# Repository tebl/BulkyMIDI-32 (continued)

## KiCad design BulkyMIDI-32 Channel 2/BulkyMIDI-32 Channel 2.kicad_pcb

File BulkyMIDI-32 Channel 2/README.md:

# BulkyMIDI-32 Channel 2
I know that the main *BulkyMIDI-32* has a fancy display that shows instruments and so on, the original *Roland MT-32* also did something similar back when they were still sold in music shops. However, I wanted an excuse to add a ton of LEDs to the project while having a bit of fun with older logic chips. Because, who doesn't want more blinking lights? Noone, that's who. The other channel monitor board is a bit more interesting in that it does everything with basic logic chips, but I wanted one more variant to play around - this one uses an Arduino instead.

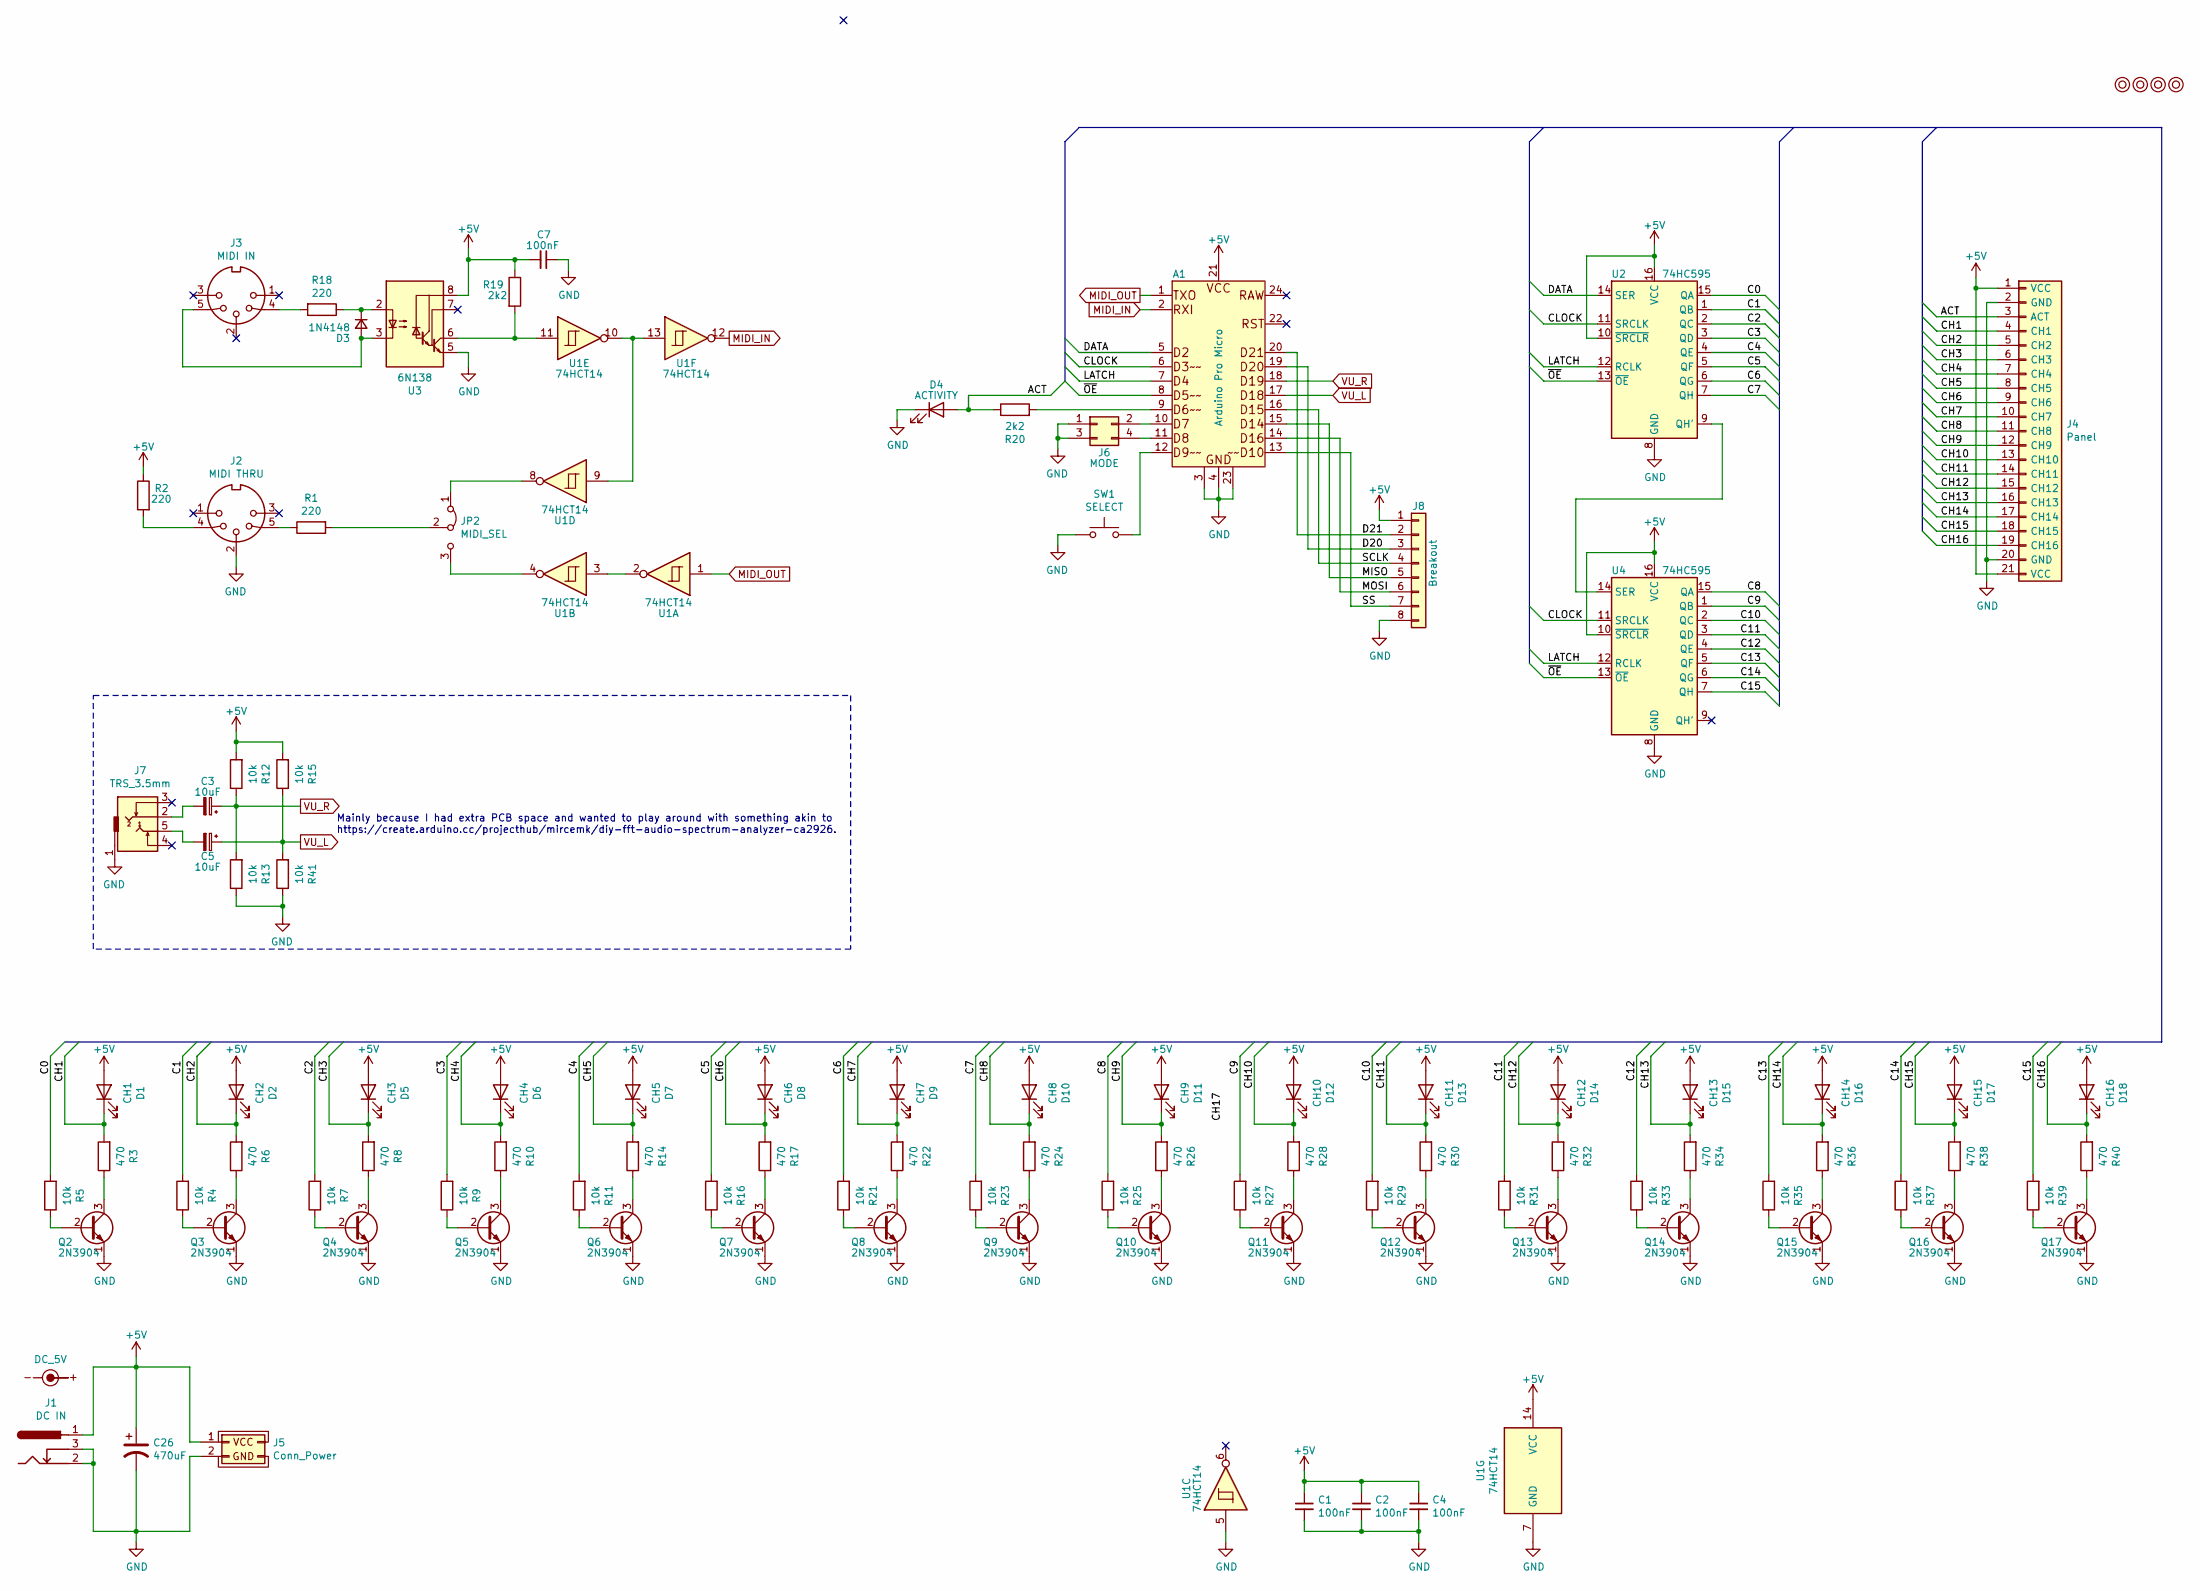
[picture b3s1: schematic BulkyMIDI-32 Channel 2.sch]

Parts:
A1: Arduino Pro Micro; Arduino_Pro_Micro
C1, C2, C4, C7: 100nF; C_Disc_D4.7mm_W2.5mm_P5.00mm
C3, C5: 10uF; CP_Radial_D4.0mm_P2.00mm
C26: 470uF; CP_Radial_D8.0mm_P3.50mm
D1: CH1; LED_D3.0mm
D2: CH2; LED_D3.0mm
D3: 1N4148; D_DO-35_SOD27_P7.62mm_Horizontal
D4: ACTIVITY; LED_D3.0mm
D5: CH3; LED_D3.0mm
D6: CH4; LED_D3.0mm
D7: CH5; LED_D3.0mm
D8: CH6; LED_D3.0mm
D9: CH7; LED_D3.0mm
D10: CH8; LED_D3.0mm
D11: CH9; LED_D3.0mm
D12: CH10; LED_D3.0mm
D13: CH11; LED_D3.0mm
D14: CH12; LED_D3.0mm
D15: CH13; LED_D3.0mm
D16: CH14; LED_D3.0mm
D17: CH15; LED_D3.0mm
D18: CH16; LED_D3.0mm
J1: DC IN; BarrelJack_Horizontal
J2: MIDI THRU; DIN5_MIDI
J3: MIDI IN; DIN5_MIDI
J4: Panel; Channel_Panel
J5: Conn_Power
J6: MODE; PinHeader_2x02_P2.54mm_Horizontal
J7: TRS_3.5mm; Tayda_3.5mm_stereo_TRS_jack_A-853
J8: Breakout; PinHeader_1x08_P2.54mm_Vertical
JP2: MIDI_SEL; PinHeader_1x03_P2.54mm_Horizontal
M1, M2, M3, M4: Mounting; M3
Q2, Q3, Q4, Q5, Q6, Q7, Q8, Q9, Q10, Q11, Q12, Q13, Q14, Q15, Q16, Q17: 2N3904; TO-92_Inline_Wide
R1, R2, R18: 220; R_Axial_DIN0207_L6.3mm_D2.5mm_P10.16mm_Horizontal
R3, R6, R8, R10, R14, R17, R22, R24, R26, R28, R30, R32, R34, R36, R38, R40: 470; R_Axial_DIN0207_L6.3mm_D2.5mm_P10.16mm_Horizontal
R4, R5, R7, R9, R11, R12, R13, R15, R16, R21, R23, R25, R27, R29, R31, R33, R35, R37, R39, R41: 10k; R_Axial_DIN0207_L6.3mm_D2.5mm_P10.16mm_Horizontal
R19, R20: 2k2; R_Axial_DIN0207_L6.3mm_D2.5mm_P10.16mm_Horizontal
SW1: SELECT; SW_Tactile_SPST_Angled_PTS645Vx39-2LFS
SYM1: DC_5V; PWR_Specification
U1: 74HCT14; DIP-14_W7.62mm_Socket_LongPads
U2, U4: 74HC595; DIP-16_W7.62mm_Socket_LongPads
U3: 6N138; DIP-8_W7.62mm_Socket_LongPads

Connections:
+5V: A1.21 (VCC), C1.1, C2.1, C4.1, C7.2, C26.1, D1.2 (A), D2.2 (A), D5.2 (A), D6.2 (A), D7.2 (A), D8.2 (A), D9.2 (A), D10.2 (A), D11.2 (A), D12.2 (A), D13.2 (A), D14.2 (A), D15.2 (A), D16.2 (A), D17.2 (A), D18.2 (A), J1.1, J4.1 (VCC), J4.21 (VCC), J5.1 (VCC), J8.1, R2.1, R12.2, R15.2, R19.1, U1.14 (VCC), U2.10 (~SRCLR), U2.16 (VCC), U3.8 (VCC), U4.10 (~SRCLR), U4.16 (VCC)
/ACT: D4.2 (A), J4.3 (ACT), R20.1
/C0: R5.2, U2.15 (QA)
/C1: R4.2, U2.1 (QB)
/C2: R7.2, U2.2 (QC)
/C3: R9.2, U2.3 (QD)
/C4: R11.2, U2.4 (QE)
/C5: R16.2, U2.5 (QF)
/C6: R21.2, U2.6 (QG)
/C7: R23.2, U2.7 (QH)
/C8: R25.2, U4.15 (QA)
/C9: R27.2, U4.1 (QB)
/C10: R29.2, U4.2 (QC)
/C11: R31.2, U4.3 (QD)
/C12: R33.2, U4.4 (QE)
/C13: R35.2, U4.5 (QF)
/C14: R37.2, U4.6 (QG)
/C15: R39.2, U4.7 (QH)
/CH1: D1.1 (K), J4.4 (CH1), R3.2
/CH2: D2.1 (K), J4.5 (CH2), R6.2
/CH3: D5.1 (K), J4.6 (CH3), R8.2
/CH4: D6.1 (K), J4.7 (CH4), R10.2
/CH5: D7.1 (K), J4.8 (CH5), R14.2
/CH6: D8.1 (K), J4.9 (CH6), R17.2
/CH7: D9.1 (K), J4.10 (CH7), R22.2
/CH8: D10.1 (K), J4.11 (CH8), R24.2
/CH9: D11.1 (K), J4.12 (CH9), R26.2
/CH10: D12.1 (K), J4.13 (CH10), R28.2
/CH11: D13.1 (K), J4.14 (CH11), R30.2
/CH12: D14.1 (K), J4.15 (CH12), R32.2
/CH13: D15.1 (K), J4.16 (CH13), R34.2
/CH14: D16.1 (K), J4.17 (CH14), R36.2
/CH15: D17.1 (K), J4.18 (CH15), R38.2
/CH16: D18.1 (K), J4.19 (CH16), R40.2
/CLOCK: A1.6 (D3), U2.11 (SRCLK), U4.11 (SRCLK)
/D20: A1.19 (D20), J8.3
/D21: A1.20 (D21), J8.2
/DATA: A1.5 (D2), U2.14 (SER)
/LATCH: A1.7 (D4), U2.12 (RCLK), U4.12 (RCLK)
/MISO: A1.15 (D14), J8.5
/MOSI: A1.14 (D16), J8.6
/SCLK: A1.16 (D15), J8.4
/SS: A1.13 (D10), J8.7
/~OE: A1.8 (D5), U2.13 (~OE), U4.13 (~OE)
GND: A1.3 (GND), A1.4 (GND), A1.23 (GND), C1.2, C2.2, C4.2, C7.1, C26.2, D4.1 (K), J1.2, J1.3, J2.2, J4.2 (GND), J4.20 (GND), J5.2 (GND), J6.1, J6.3, J7.1, J8.8, Q2.1 (E), Q3.1 (E), Q4.1 (E), Q5.1 (E), Q6.1 (E), Q7.1 (E), Q8.1 (E), Q9.1 (E), Q10.1 (E), Q11.1 (E), Q12.1 (E), Q13.1 (E), Q14.1 (E), Q15.1 (E), Q16.1 (E), Q17.1 (E), R13.1, R41.1, SW1.1, U1.5, U1.7 (GND), U2.8 (GND), U3.5 (GND), U4.8 (GND)
MIDI_IN: A1.2 (RXI), U1.12
MIDI_OUT: A1.1 (TXO), U1.1
unnamed: A1.9 (D6), R20.2
unnamed: A1.10 (D7), J6.2
unnamed: A1.11 (D8), J6.4
unnamed: A1.12 (D9), SW1.2
unnamed: C3.2, J7.2
unnamed: C5.2, J7.5
unnamed: D3.1 (K), R18.1, U3.2 (C1)
unnamed: D3.2 (A), J3.5, U3.3 (C2)
unnamed: J2.4, R2.2
unnamed: J2.5, R1.1
unnamed: J3.4, R18.2
unnamed: JP2.1 (A), U1.8
unnamed: JP2.2 (C), R1.2
unnamed: JP2.3 (B), U1.4
unnamed: Q2.2 (B), R5.1
unnamed: Q2.3 (C), R3.1
unnamed: Q3.2 (B), R4.1
unnamed: Q3.3 (C), R6.1
unnamed: Q4.2 (B), R7.1
unnamed: Q4.3 (C), R8.1
unnamed: Q5.2 (B), R9.1
unnamed: Q5.3 (C), R10.1
unnamed: Q6.2 (B), R11.1
unnamed: Q6.3 (C), R14.1
unnamed: Q7.2 (B), R16.1
unnamed: Q7.3 (C), R17.1
unnamed: Q8.2 (B), R21.1
unnamed: Q8.3 (C), R22.1
unnamed: Q9.2 (B), R23.1
unnamed: Q9.3 (C), R24.1
unnamed: Q10.2 (B), R25.1
unnamed: Q10.3 (C), R26.1
unnamed: Q11.2 (B), R27.1
unnamed: Q11.3 (C), R28.1
unnamed: Q12.2 (B), R29.1
unnamed: Q12.3 (C), R30.1
unnamed: Q13.2 (B), R31.1
unnamed: Q13.3 (C), R32.1
unnamed: Q14.2 (B), R33.1
unnamed: Q14.3 (C), R34.1
unnamed: Q15.2 (B), R35.1
unnamed: Q15.3 (C), R36.1
unnamed: Q16.2 (B), R37.1
unnamed: Q16.3 (C), R38.1
unnamed: Q17.2 (B), R39.1
unnamed: Q17.3 (C), R40.1
unnamed: R19.2, U1.11, U3.6 (VO2)
unnamed: U1.2, U1.3
unnamed: U1.9, U1.10, U1.13
unnamed: U2.9 (QH'), U4.14 (SER)
VU_L: A1.17 (D18), C5.1, R15.1, R41.2
VU_R: A1.18 (D19), C3.1, R12.1, R13.2

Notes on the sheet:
Mainly because I had extra PCB space and wanted to play around with something akin to https://create.arduino.cc/projecthub/mircemk/diy-fft-audio-spectrum-analyzer-ca2926.

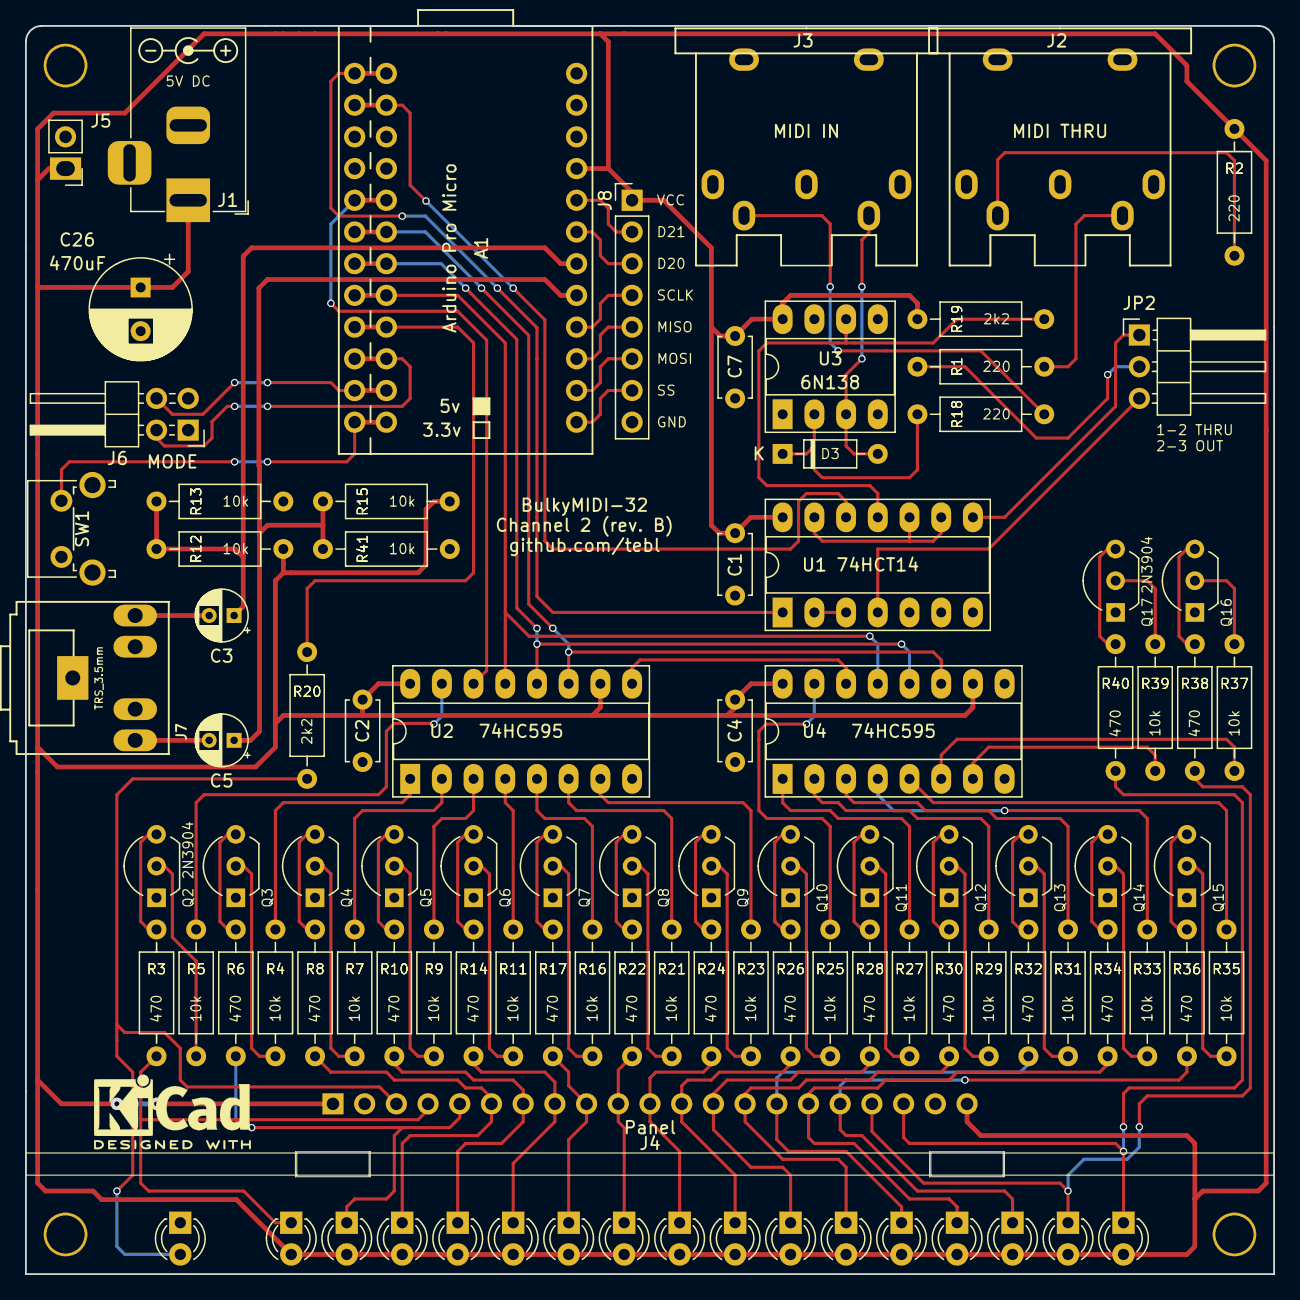
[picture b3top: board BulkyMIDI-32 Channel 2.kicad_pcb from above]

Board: 2 copper layers, 100.0 x 100.0 mm, 102 parts (0 on the bottom side), 99 nets.

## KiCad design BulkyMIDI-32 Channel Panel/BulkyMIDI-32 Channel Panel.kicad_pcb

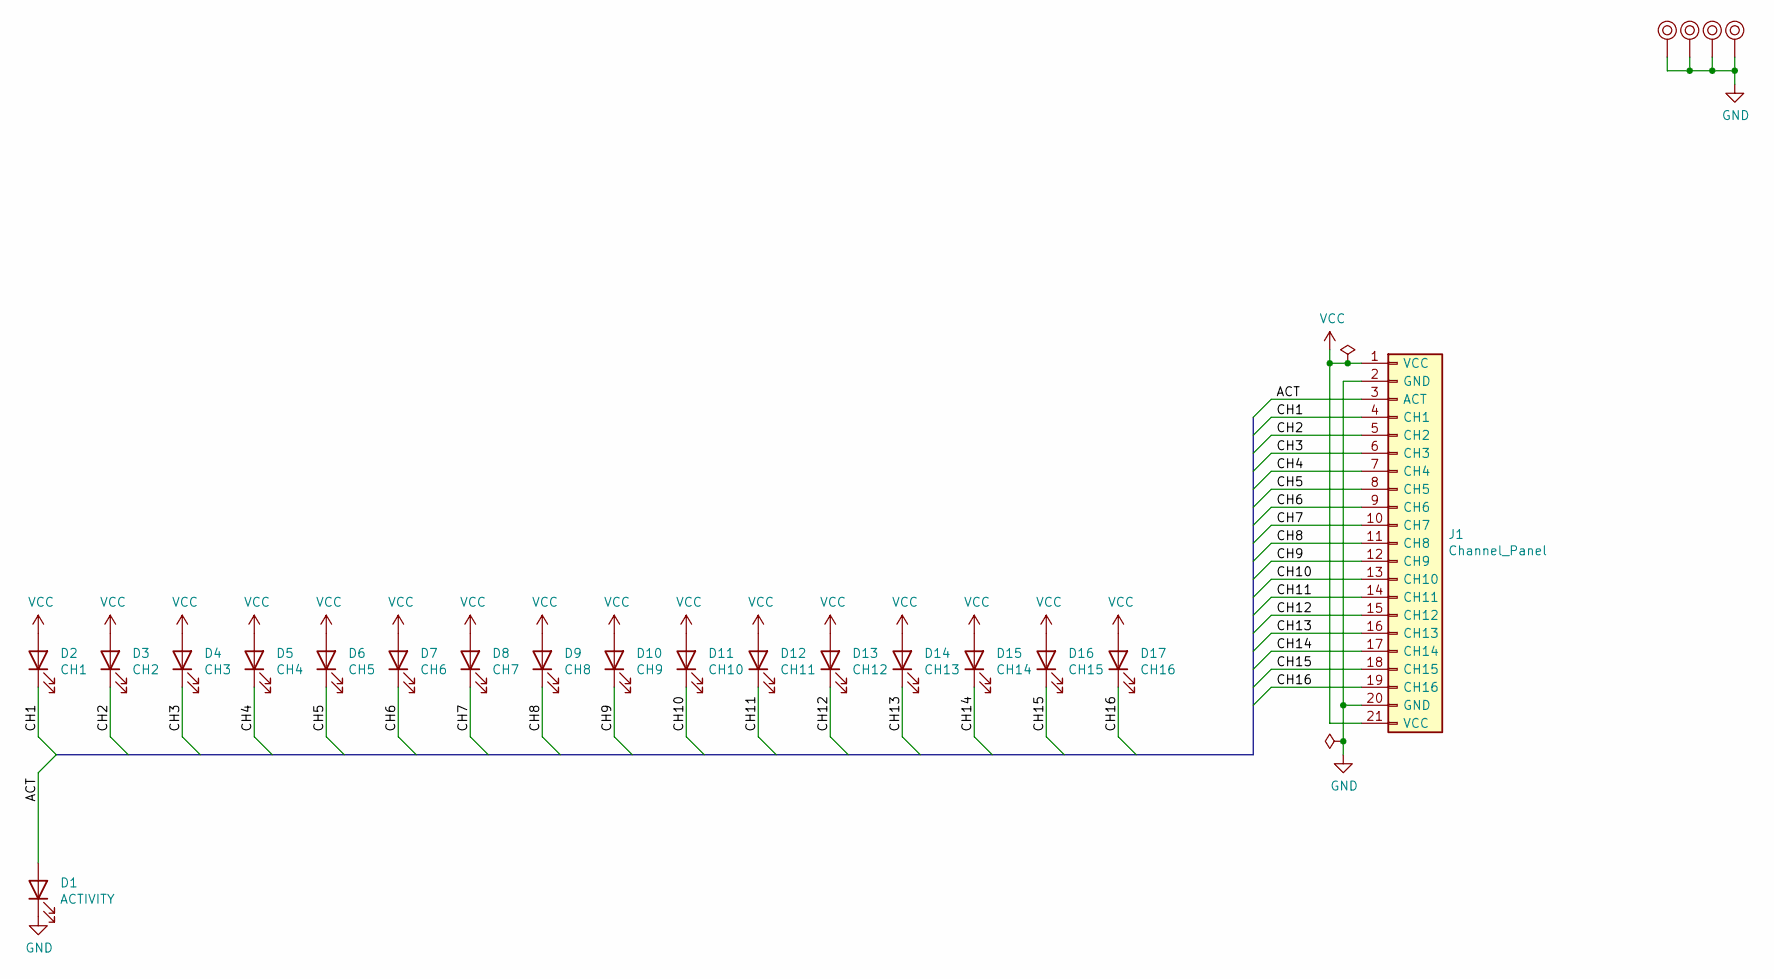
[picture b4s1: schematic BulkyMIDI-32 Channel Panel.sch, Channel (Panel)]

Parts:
D1: ACTIVITY; LED_D5.0mm
D2: CH1; LED_D5.0mm
D3: CH2; LED_D5.0mm
D4: CH3; LED_D5.0mm
D5: CH4; LED_D5.0mm
D6: CH5; LED_D5.0mm
D7: CH6; LED_D5.0mm
D8: CH7; LED_D5.0mm
D9: CH8; LED_D5.0mm
D10: CH9; LED_D5.0mm
D11: CH10; LED_D5.0mm
D12: CH11; LED_D5.0mm
D13: CH12; LED_D5.0mm
D14: CH13; LED_D5.0mm
D15: CH14; LED_D5.0mm
D16: CH15; LED_D5.0mm
D17: CH16; LED_D5.0mm
J1: Channel_Panel; PinHeader_1x21_P2.54mm_Horizontal
M1, M2, M3, M4: Mounting_Pin; M3_pin

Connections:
/ACT: D1.2 (A), J1.3 (ACT)
/CH1: D2.1 (K), J1.4 (CH1)
/CH2: D3.1 (K), J1.5 (CH2)
/CH3: D4.1 (K), J1.6 (CH3)
/CH4: D5.1 (K), J1.7 (CH4)
/CH5: D6.1 (K), J1.8 (CH5)
/CH6: D7.1 (K), J1.9 (CH6)
/CH7: D8.1 (K), J1.10 (CH7)
/CH8: D9.1 (K), J1.11 (CH8)
/CH9: D10.1 (K), J1.12 (CH9)
/CH10: D11.1 (K), J1.13 (CH10)
/CH11: D12.1 (K), J1.14 (CH11)
/CH12: D13.1 (K), J1.15 (CH12)
/CH13: D14.1 (K), J1.16 (CH13)
/CH14: D15.1 (K), J1.17 (CH14)
/CH15: D16.1 (K), J1.18 (CH15)
/CH16: D17.1 (K), J1.19 (CH16)
GND: D1.1 (K), J1.2 (GND), J1.20 (GND), M1.1, M2.1, M3.1, M4.1
VCC: D2.2 (A), D3.2 (A), D4.2 (A), D5.2 (A), D6.2 (A), D7.2 (A), D8.2 (A), D9.2 (A), D10.2 (A), D11.2 (A), D12.2 (A), D13.2 (A), D14.2 (A), D15.2 (A), D16.2 (A), D17.2 (A), J1.1 (VCC), J1.21 (VCC)

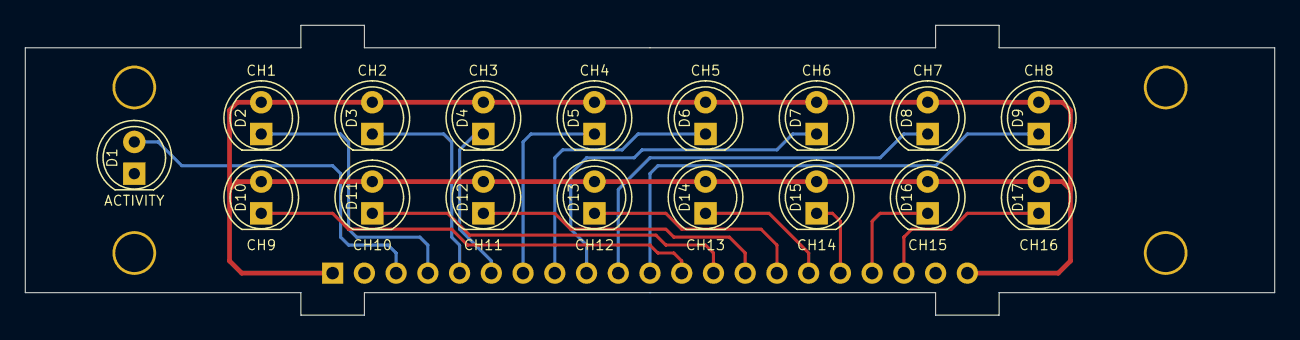
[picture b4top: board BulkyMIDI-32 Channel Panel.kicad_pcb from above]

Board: 2 copper layers, 100.0 x 23.2 mm, 22 parts (1 on the bottom side), 19 nets.

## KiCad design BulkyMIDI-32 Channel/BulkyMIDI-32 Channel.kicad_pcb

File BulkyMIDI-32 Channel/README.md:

# BulkyMIDI-32 Channel
I know that the main *BulkyMIDI-32* has a fancy display that shows instruments and so on, the original *Roland MT-32* also did something similar back when they were still sold in music shops. However, I wanted an excuse to add a ton of LEDs to the project while having a bit of fun with older logic chips. Because, who doesn't want more blinking lights? Noone, that's who. My starting point was an article by W. Dunczewski, titled *MIDI Channel Monitor* that was printed in the [ october 1993](https://worldradiohistory.com/Elektor.htm) issue of *Elektor Electronics*.

While the low-level description of the circuit details is better left to the article itself, I'll only make a brave attempt at describing what it actually aims to accomplish; The purpose of the board is to light up an LED corresponding to each MIDI-channel, but instead of doing it as yet another Arduino-based design - it implements this using using basic logic chips and counters. It does this by waiting for a digital MIDI-message, then picks out the bits that specifies the channel.

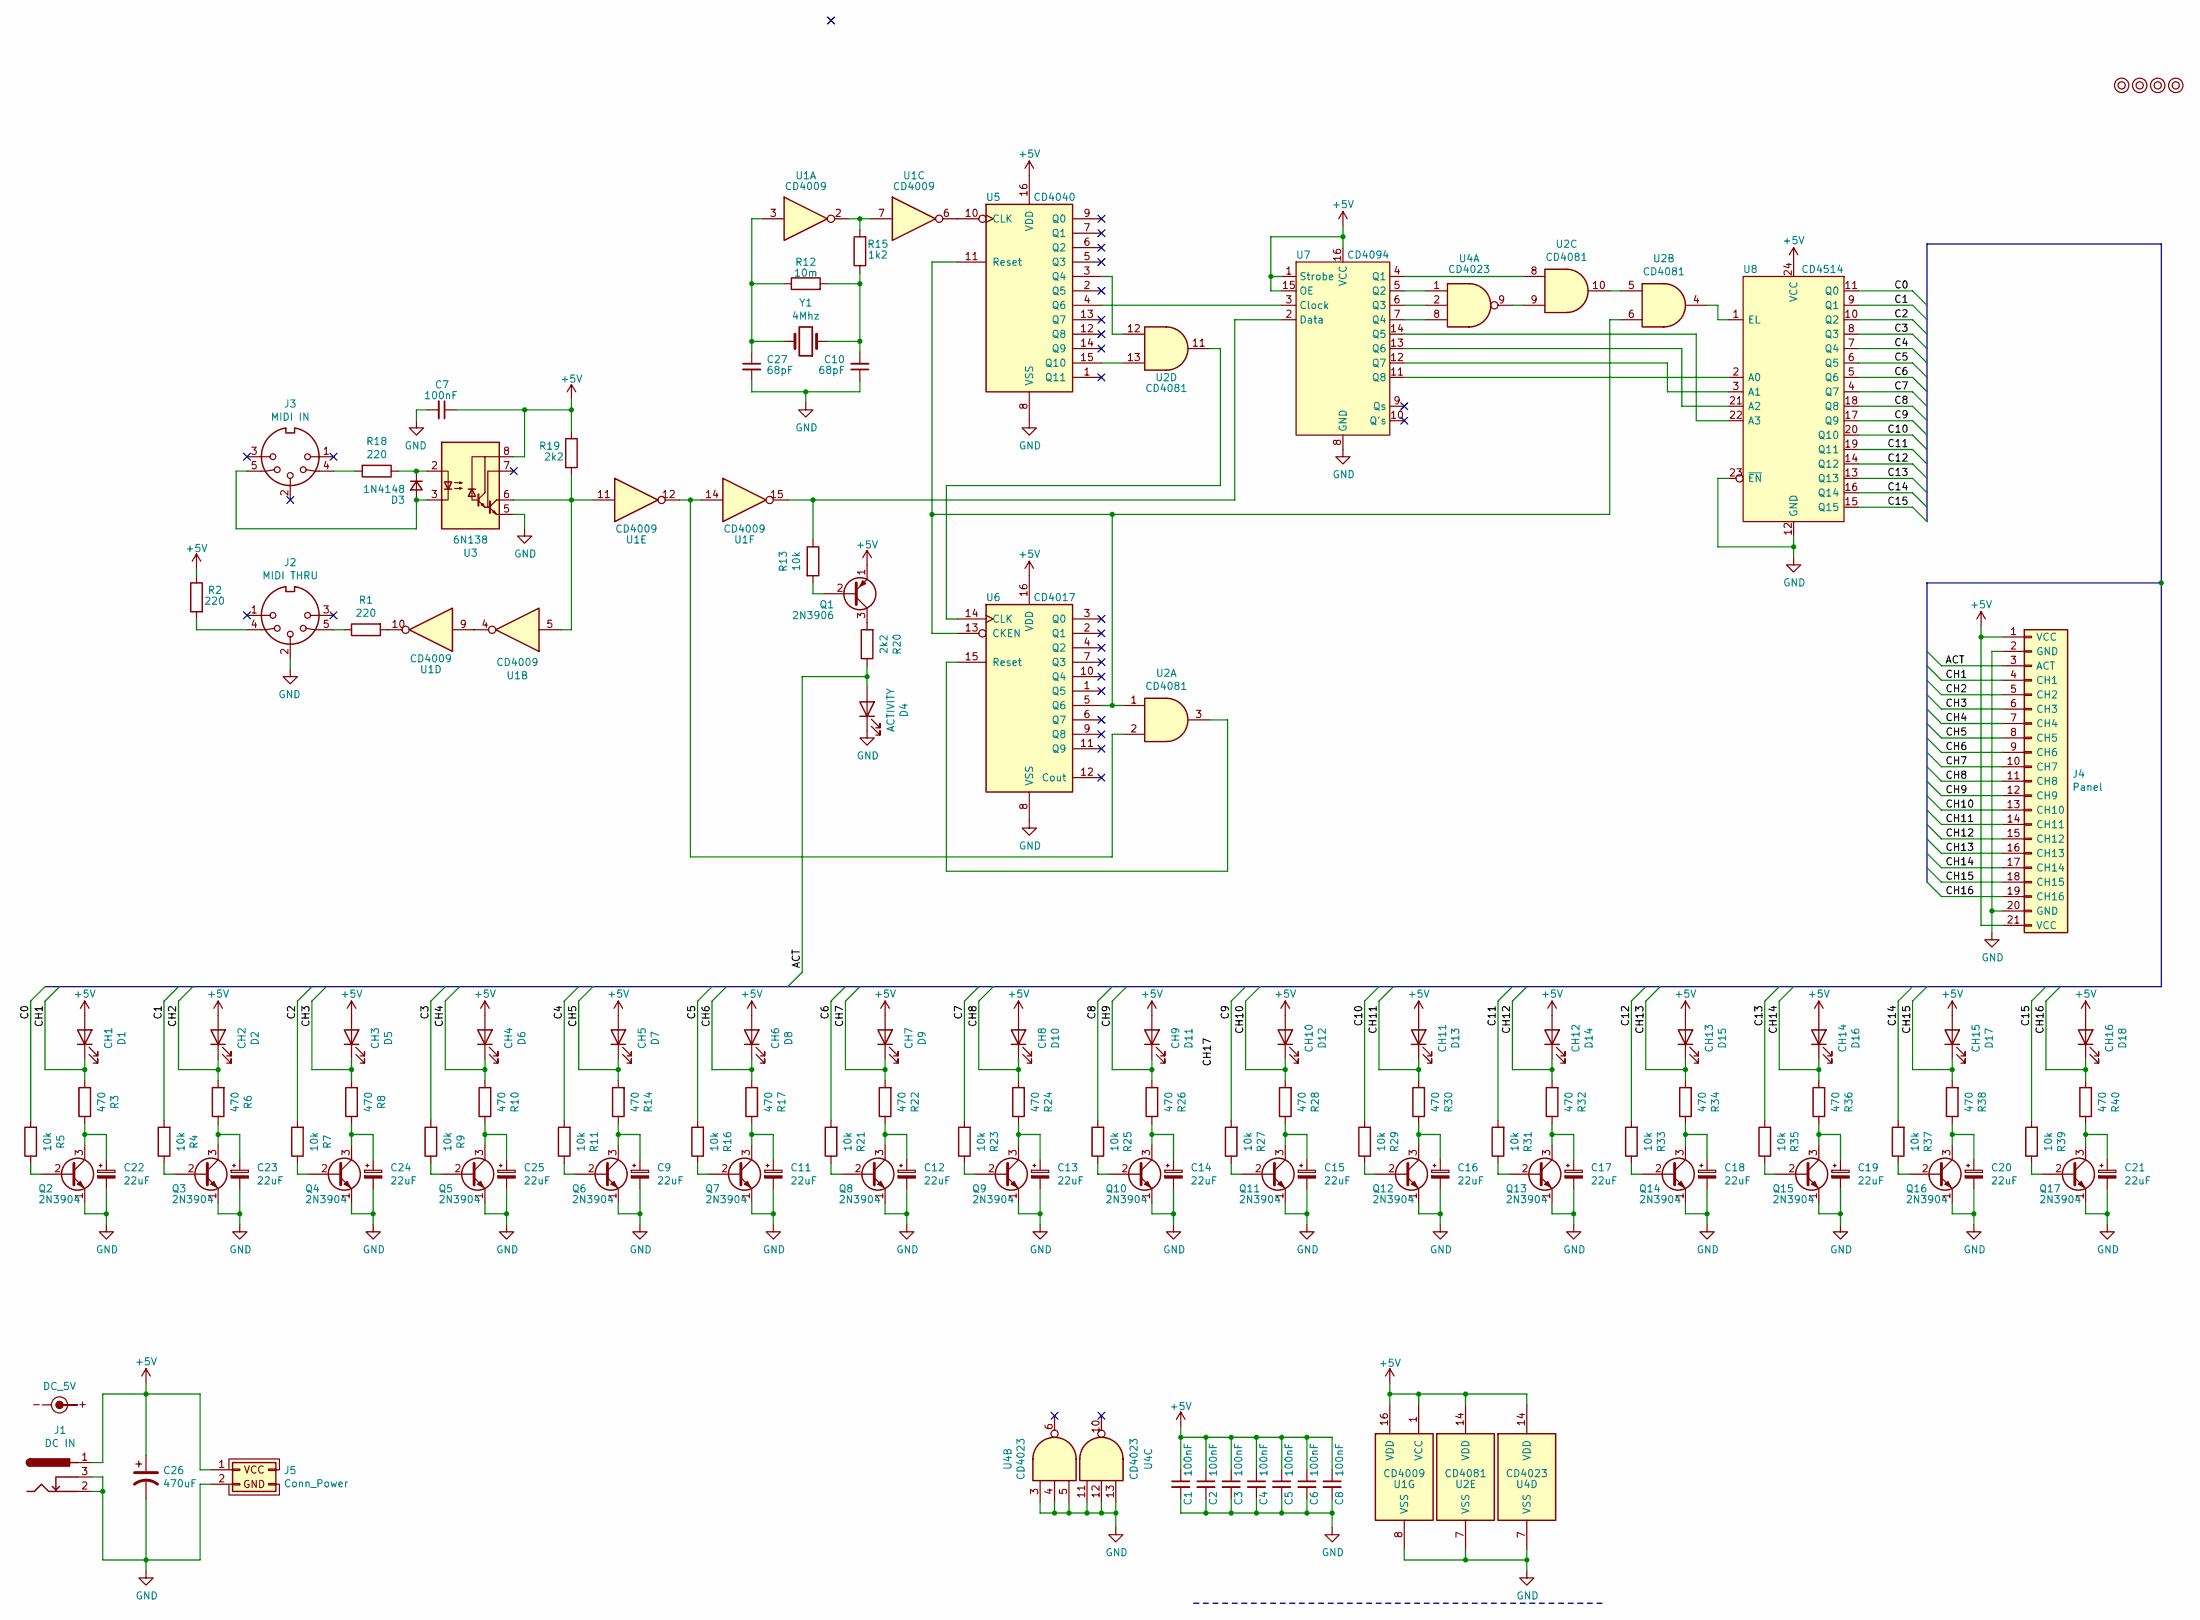
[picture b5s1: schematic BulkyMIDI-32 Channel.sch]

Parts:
C1, C2, C3, C4, C5, C6, C7, C8: 100nF; C_Disc_D4.7mm_W2.5mm_P5.00mm
C9, C11, C12, C13, C14, C15, C16, C17, C18, C19, C20, C21, C22, C23, C24, C25: 22uF; CP_Radial_D5.0mm_P2.00mm
C10, C27: 68pF; C_Disc_D4.7mm_W2.5mm_P5.00mm
C26: 470uF; CP_Radial_D8.0mm_P3.50mm
D1: CH1; LED_D3.0mm
D2: CH2; LED_D3.0mm
D3: 1N4148; D_DO-35_SOD27_P7.62mm_Horizontal
D4: ACTIVITY; LED_D3.0mm
D5: CH3; LED_D3.0mm
D6: CH4; LED_D3.0mm
D7: CH5; LED_D3.0mm
D8: CH6; LED_D3.0mm
D9: CH7; LED_D3.0mm
D10: CH8; LED_D3.0mm
D11: CH9; LED_D3.0mm
D12: CH10; LED_D3.0mm
D13: CH11; LED_D3.0mm
D14: CH12; LED_D3.0mm
D15: CH13; LED_D3.0mm
D16: CH14; LED_D3.0mm
D17: CH15; LED_D3.0mm
D18: CH16; LED_D3.0mm
J1: DC IN; BARREL_JACK
J2: MIDI THRU; DIN5_MIDI
J3: MIDI IN; DIN5_MIDI
J4: Panel; Channel_Panel
J5: Conn_Power
M1, M2, M3, M4: Mounting; M3
Q1: 2N3906; TO-92_Inline_Wide
Q2, Q3, Q4, Q5, Q6, Q7, Q8, Q9, Q10, Q11, Q12, Q13, Q14, Q15, Q16, Q17: 2N3904; TO-92_Inline_Wide
R1, R2, R18: 220; R_Axial_DIN0207_L6.3mm_D2.5mm_P10.16mm_Horizontal
R3, R6, R8, R10, R14, R17, R22, R24, R26, R28, R30, R32, R34, R36, R38, R40: 470; R_Axial_DIN0207_L6.3mm_D2.5mm_P10.16mm_Horizontal
R4, R5, R7, R9, R11, R13, R16, R21, R23, R25, R27, R29, R31, R33, R35, R37, R39: 10k; R_Axial_DIN0207_L6.3mm_D2.5mm_P10.16mm_Horizontal
R12: 10m; R_Axial_DIN0207_L6.3mm_D2.5mm_P10.16mm_Horizontal
R15: 1k2; R_Axial_DIN0207_L6.3mm_D2.5mm_P10.16mm_Horizontal
R19, R20: 2k2; R_Axial_DIN0207_L6.3mm_D2.5mm_P10.16mm_Horizontal
SYM1: DC_5V; PWR_Specification
U1: CD4009; DIP-16_W7.62mm_Socket_LongPads
U2: CD4081; DIP-14_W7.62mm_Socket_LongPads
U3: 6N138; DIP-8_W7.62mm_Socket_LongPads
U4: CD4023; DIP-14_W7.62mm_Socket_LongPads
U5: CD4040; DIP-16_W7.62mm_Socket_LongPads
U6: CD4017; DIP-16_W7.62mm_Socket_LongPads
U7: CD4094; DIP-16_W7.62mm_Socket_LongPads
U8: CD4514; DIP-24_W15.24mm_Socket_LongPads
Y1: 4Mhz; Crystal_HC49-U_Vertical

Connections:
+5V: C1.1, C2.1, C3.1, C4.1, C5.1, C6.1, C7.1, C8.1, C26.1, D1.2 (A), D2.2 (A), D5.2 (A), D6.2 (A), D7.2 (A), D8.2 (A), D9.2 (A), D10.2 (A), D11.2 (A), D12.2 (A), D13.2 (A), D14.2 (A), D15.2 (A), D16.2 (A), D17.2 (A), D18.2 (A), J1.1, J4.1 (VCC), J4.21 (VCC), J5.1 (VCC), Q1.1 (E), R2.1, R19.1, U1.1 (VCC), U1.16 (VDD), U2.14 (VDD), U3.8 (VCC), U4.14 (VDD), U5.16 (VDD), U6.16 (VDD), U7.1 (Strobe), U7.15 (OE), U7.16 (VCC), U8.24 (VCC)
/ACT: D4.2 (A), J4.3 (ACT), R20.1
/C0: R5.2, U8.11 (Q0)
/C1: R4.2, U8.9 (Q1)
/C2: R7.2, U8.10 (Q2)
/C3: R9.2, U8.8 (Q3)
/C4: R11.2, U8.7 (Q4)
/C5: R16.2, U8.6 (Q5)
/C6: R21.2, U8.5 (Q6)
/C7: R23.2, U8.4 (Q7)
/C8: R25.2, U8.18 (Q8)
/C9: R27.2, U8.17 (Q9)
/C10: R29.2, U8.20 (Q10)
/C11: R31.2, U8.19 (Q11)
/C12: R33.2, U8.14 (Q12)
/C13: R35.2, U8.13 (Q13)
/C14: R37.2, U8.16 (Q14)
/C15: R39.2, U8.15 (Q15)
/CH1: D1.1 (K), J4.4 (CH1), R3.2
/CH2: D2.1 (K), J4.5 (CH2), R6.2
/CH3: D5.1 (K), J4.6 (CH3), R8.2
/CH4: D6.1 (K), J4.7 (CH4), R10.2
/CH5: D7.1 (K), J4.8 (CH5), R14.2
/CH6: D8.1 (K), J4.9 (CH6), R17.2
/CH7: D9.1 (K), J4.10 (CH7), R22.2
/CH8: D10.1 (K), J4.11 (CH8), R24.2
/CH9: D11.1 (K), J4.12 (CH9), R26.2
/CH10: D12.1 (K), J4.13 (CH10), R28.2
/CH11: D13.1 (K), J4.14 (CH11), R30.2
/CH12: D14.1 (K), J4.15 (CH12), R32.2
/CH13: D15.1 (K), J4.16 (CH13), R34.2
/CH14: D16.1 (K), J4.17 (CH14), R36.2
/CH15: D17.1 (K), J4.18 (CH15), R38.2
/CH16: D18.1 (K), J4.19 (CH16), R40.2
GND: C1.2, C2.2, C3.2, C4.2, C5.2, C6.2, C7.2, C8.2, C9.2, C10.1, C11.2, C12.2, C13.2, C14.2, C15.2, C16.2, C17.2, C18.2, C19.2, C20.2, C21.2, C22.2, C23.2, C24.2, C25.2, C26.2, C27.2, D4.1 (K), J1.2, J1.3, J2.2, J4.2 (GND), J4.20 (GND), J5.2 (GND), Q2.1 (E), Q3.1 (E), Q4.1 (E), Q5.1 (E), Q6.1 (E), Q7.1 (E), Q8.1 (E), Q9.1 (E), Q10.1 (E), Q11.1 (E), Q12.1 (E), Q13.1 (E), Q14.1 (E), Q15.1 (E), Q16.1 (E), Q17.1 (E), U1.8 (VSS), U2.7 (VSS), U3.5 (GND), U4.3, U4.4, U4.5, U4.7 (VSS), U4.11, U4.12, U4.13, U5.8 (VSS), U6.8 (VSS), U7.8 (GND), U8.12 (GND), U8.23 (~EN)
unnamed: C9.1, Q6.3 (C), R14.1
unnamed: C10.2, R12.2, R15.1, Y1.1
unnamed: C11.1, Q7.3 (C), R17.1
unnamed: C12.1, Q8.3 (C), R22.1
unnamed: C13.1, Q9.3 (C), R24.1
unnamed: C14.1, Q10.3 (C), R26.1
unnamed: C15.1, Q11.3 (C), R28.1
unnamed: C16.1, Q12.3 (C), R30.1
unnamed: C17.1, Q13.3 (C), R32.1
unnamed: C18.1, Q14.3 (C), R34.1
unnamed: C19.1, Q15.3 (C), R36.1
unnamed: C20.1, Q16.3 (C), R38.1
unnamed: C21.1, Q17.3 (C), R40.1
unnamed: C22.1, Q2.3 (C), R3.1
unnamed: C23.1, Q3.3 (C), R6.1
unnamed: C24.1, Q4.3 (C), R8.1
unnamed: C25.1, Q5.3 (C), R10.1
unnamed: C27.1, R12.1, U1.3, Y1.2
unnamed: D3.1 (K), R18.1, U3.2 (C1)
unnamed: D3.2 (A), J3.5, U3.3 (C2)
unnamed: J2.4, R2.2
unnamed: J2.5, R1.1
unnamed: J3.4, R18.2
unnamed: Q1.2 (B), R13.2
unnamed: Q1.3 (C), R20.2
unnamed: Q2.2 (B), R5.1
unnamed: Q3.2 (B), R4.1
unnamed: Q4.2 (B), R7.1
unnamed: Q5.2 (B), R9.1
unnamed: Q6.2 (B), R11.1
unnamed: Q7.2 (B), R16.1
unnamed: Q8.2 (B), R21.1
unnamed: Q9.2 (B), R23.1
unnamed: Q10.2 (B), R25.1
unnamed: Q11.2 (B), R27.1
unnamed: Q12.2 (B), R29.1
unnamed: Q13.2 (B), R31.1
unnamed: Q14.2 (B), R33.1
unnamed: Q15.2 (B), R35.1
unnamed: Q16.2 (B), R37.1
unnamed: Q17.2 (B), R39.1
unnamed: R1.2, U1.10
unnamed: R13.1, U1.15, U7.2 (Data)
unnamed: R15.2, U1.2, U1.7
unnamed: R19.2, U1.5, U1.11, U3.6 (VO2)
unnamed: U1.4, U1.9
unnamed: U1.6, U5.10 (CLK)
unnamed: U1.12, U1.14, U2.2
unnamed: U2.1, U2.6, U5.11 (Reset), U6.5 (Q6), U6.13 (CKEN)
unnamed: U2.3, U6.15 (Reset)
unnamed: U2.4, U8.1 (EL)
unnamed: U2.8, U7.4 (Q1)
unnamed: U2.9, U4.9
unnamed: U2.5, U2.10
unnamed: U2.11, U6.14 (CLK)
unnamed: U2.12, U5.3 (Q4)
unnamed: U2.13, U5.15 (Q10)
unnamed: U4.1, U7.5 (Q2)
unnamed: U4.2, U7.6 (Q3)
unnamed: U4.8, U7.7 (Q4)
unnamed: U5.4 (Q6), U7.3 (Clock)
unnamed: U7.11 (Q8), U8.2 (A0)
unnamed: U7.12 (Q7), U8.3 (A1)
unnamed: U7.13 (Q6), U8.21 (A2)
unnamed: U7.14 (Q5), U8.22 (A3)

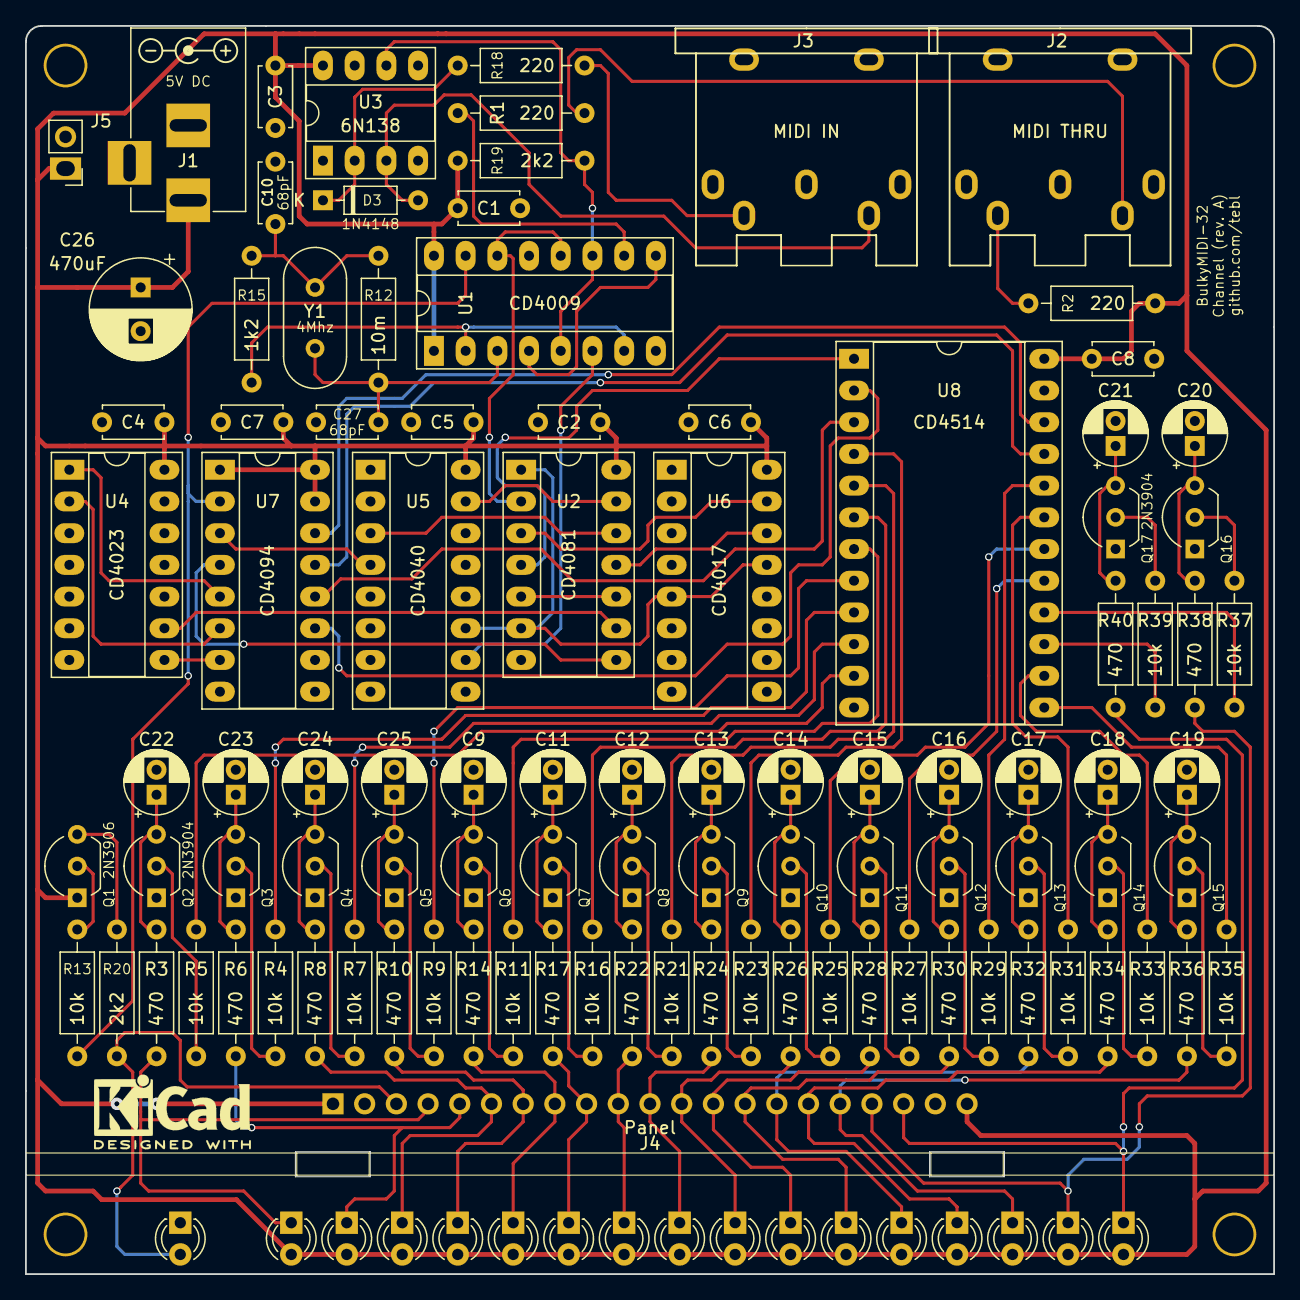
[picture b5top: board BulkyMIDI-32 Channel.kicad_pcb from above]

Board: 2 copper layers, 100.0 x 100.0 mm, 121 parts (0 on the bottom side), 100 nets.

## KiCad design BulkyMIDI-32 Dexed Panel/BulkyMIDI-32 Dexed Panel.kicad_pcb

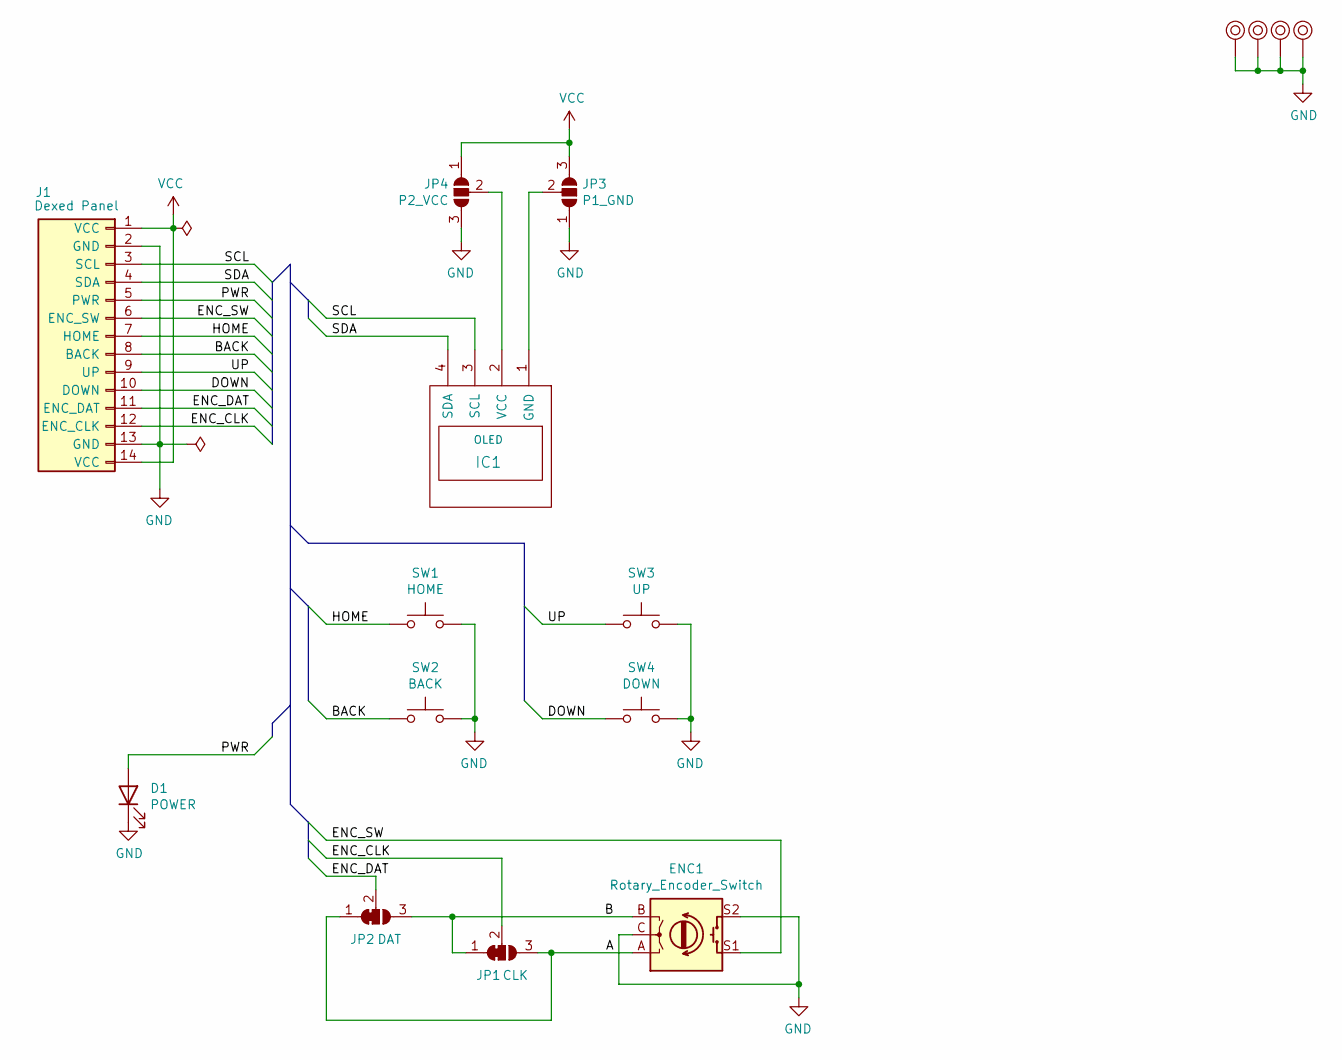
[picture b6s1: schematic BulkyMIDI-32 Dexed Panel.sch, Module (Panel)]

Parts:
D1: POWER; LED_D5.0mm
ENC1: Rotary_Encoder_Switch; RotaryEncoder_Alps_EC11E-Switch_Vertical_H20mm
IC1: OLED; 1.3_I2C_OLED_No_mounting
J1: Dexed Panel; PinHeader_1x14_P2.54mm_Horizontal
JP1: CLK; SolderJumper-3_P1.3mm_Open_Pad1.0x1.5mm
JP2: DAT; SolderJumper-3_P1.3mm_Open_Pad1.0x1.5mm
JP3: P1_GND; SolderJumper-3_P1.3mm_Open_Pad1.0x1.5mm
JP4: P2_VCC; SolderJumper-3_P1.3mm_Open_Pad1.0x1.5mm
M1, M2, M3, M4: Mounting_Pin; M3_pin
SW1: HOME; SW_PUSH_6mm
SW2: BACK; SW_PUSH_6mm
SW3: UP; SW_PUSH_6mm
SW4: DOWN; SW_PUSH_6mm

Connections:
/A: ENC1.A, JP1.3 (B), JP2.1 (A)
/B: ENC1.B, JP1.1 (A), JP2.3 (B)
/BACK: J1.8 (BACK), SW2.1
/DOWN: J1.10 (DOWN), SW4.1
/ENC_CLK: J1.12 (ENC_CLK), JP1.2 (C)
/ENC_DAT: J1.11 (ENC_DAT), JP2.2 (C)
/ENC_SW: ENC1.S1, J1.6 (ENC_SW)
/HOME: J1.7 (HOME), SW1.1
/PWR: D1.2 (A), J1.5 (PWR)
/SCL: IC1.3 (SCL), J1.3 (SCL)
/SDA: IC1.4 (SDA), J1.4 (SDA)
/UP: J1.9 (UP), SW3.1
GND: D1.1 (K), ENC1.C, ENC1.S2, J1.2 (GND), J1.13 (GND), JP3.1 (A), JP4.3 (B), M1.1, M2.1, M3.1, M4.1, SW1.2, SW2.2, SW3.2, SW4.2
unnamed: IC1.1 (GND), JP3.2 (C)
unnamed: IC1.2 (VCC), JP4.2 (C)
VCC: J1.1 (VCC), J1.14 (VCC), JP3.3 (B), JP4.1 (A)
